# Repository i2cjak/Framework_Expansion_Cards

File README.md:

# i2cjak on X.com is THE foremost hardware engineer and poaster. he is designing one (1) new Framework Expansion Card per day until they give him a REALLY NICE laptop

# PROOF OF CHALLENGE!

## [Day 1](./Day_01_Wi-Fi-HaLow/)

Wi-Fi HaLow

## [Day 2](./Day_02_Four_Port_USB_C/)

Four Port USB-C

## [Day 3](./Day_03_ECG_SPO2/)

Electrocardiogram + SPO2

## [Day 4](./Day_04_Frameoscope/)

Frameoscope

## [Day 5](./Day_05_Power_Bus_Probe/)

USB-C I2C / Qwiic Bridge & 36V / 5A Power Telemetry Probe

## [Day 6](./Day_06_Walking_Legs/)

USB SOF-Synced 2-DOF Walking Leg Controller & Mechanical Bay Linkage (`mech/`)

## [Day 7](./Day_07_Chiptune_Synth_MIDI/)

Polyphonic FM / Chiptune 32-Bit I2S Synthesizer & Type-A MIDI Out

## [Day 8](./Day_08_CAN_Bus_Analyzer/)

1 Mbps ISO-11898 CAN 2.0B Bus Analyzer (`gs_usb` SocketCAN) & PhotoMOS 120R Termination

## [Day 9](./Day_09_Radiation_Dosimeter_RNG/)

Solid-State Dual-PIN Radiation Dosimeter, Pulse Spectrometer & Quantum Decay Hardware RNG

## [Day 10](./Day_10_SWD_Debugger_UART/)

Autoleveling 1.65V–5.5V CMSIS-DAPv2 High-Speed SWD Debugger & 6 Mbps UART Console

## [Day 11](./Day_11_ToF_Gesture_IR_Blaster/)

Dual 4m Laser Time-of-Flight Stereo Gesture Deck & Universal 940nm Phased-Arc IR Blaster

## [Day 12](./Day_12_Bench_Power_Supply/)

Programmable 1.0V–15.0V (4W) SEPIC Micro Bench Power Supply, 140µs E-Fuse & 4-Wire Kelvin Port

## [Day 13](./Day_13_LoRa_Spectrum_Sweeper/)

+22 dBm Sub-GHz LoRa Mesh Radio (`SX1262`) & 150–960 MHz ISM Spectrum Sweeper w/ Edge SMA

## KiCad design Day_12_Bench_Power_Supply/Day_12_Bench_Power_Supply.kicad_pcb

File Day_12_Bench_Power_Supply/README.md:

# Day 12 — Pocket Programmable `1.0V–15.0V` SEPIC Micro Bench Supply & Electronic Fuse

A digitally trimmed pocket DC lab rail and `140 µs` hardware electronic fuse powered from a single Framework Laptop USB-C bay (`5 V` `VBUS`), delivering a regulated **`1.00 V – 15.00 V`** (`4.0 W` continuous) output with true **`0.00 V` DC shutoff**, 4-wire Kelvin voltage sensing, `16-bit` live `V/I/P` readback, and SCPI/CLI control inside a blue ENIG `26.0 × 30.0 mm` Expansion Card.

## Hardware Architecture

1. **True-Zero-Disconnect `1.2 MHz` Dual-Inductor SEPIC Stage (`U4` `MT3608`, `L1`/`L2` `SWPA4018S100MT`, `C10`, `D3` `SS34`):**
   - Unlike a conventional boost regulator—which passes `VBUS - V_D ≈ 4.7 V` straight to the output even when disabled—the **SEPIC** topology inserts a `50 V` `2.2 µF` DC-blocking coupling capacitor (`C10`) between shielded `10 µH / 1.6 A` inductors `L1` and `L2` (`4.0 × 4.0 × 1.8 mm`), providing **galvanic DC path interruption (`0.00 V` off-state)** while stepping smoothly both **below and above `5 V` `VBUS`** (`1.00 V` to `15.00 V`) into a `4× 2.2 µF / 50 V` low-ESR ceramic bank (`C11`–`C13`, `C15`) with an `18 V` `BZT52C18` overvoltage Zener clamp (`D6`).

2. **`12-Bit` DAC Feedback Injection & Closed-Loop Millivolt Trim (`U5` `MCP4725A0T-E/CH`):**
   - Injects a rail-to-rail `0–3.30 V` 12-bit DAC output (`0x60`) through `R18` (`22 kΩ 1%`) into the `MT3608` `0.600 V` feedback summing node alongside `R16` (`100 kΩ 1%` to `VOUT_SENSE`) and `R17` (`5.1 kΩ 1%` to `GND`), yielding **`3.66 mV / LSB`** native resolution across `1.00 V – 15.00 V`, continuously trimmed against `INA226` `1.25 mV` bus readback.

3. **Pulsed `25 kHz` PWM Input Soft-Start & `140 µs` Hardware Electronic Fuse (`Q1` `AO3401A`, `Q2` `AO3400A`, `U6` `INA226AIDGSR`, `R19` `50 mΩ`):**
   - Always-on `3.3 V` control power (`U2` `XC6206P332MR-G`) keeps the MCU, DAC, and telemetry alive while `Q1` (`AO3401A` high-side P-FET driven via `Q2` `AO3400A` on `PB0` / `TIM3_CH3`) precharges `C7` (`10 µF`) over `12 ms` (`< 0.15 A` peak inrush, verified via `PA1` `ADC_IN1` host `VBUS` droop sensing) and clamps continuous input draw below `0.95 A` (`4.0 W` output budget, safe on both `1.5 A` and `3.0 A` Framework USB-C ports).
   - High-side `INA226AIDGSR` (`0x40`) across `R19` (`50 mΩ 1%`, `50 µA / LSB`) fires its hardware Shunt-Over-Voltage (`SOL`) `~Alert` into `PA0` (`EXTI0`) in **`140 µs`**, killing `SEPIC_EN` (`PB1`) and opening `Q1` in `< 2 µs` ISR latency while latching the bezel `FLT` LED (`D5`).

4. **4-Wire Kelvin Bezel Output Port & Crystal-Less USB SCPI Controller (`J3` `SM04B-SRSS-TB`, `U3` `STM32F072CBT6`):**
   - Outward 4-pin `1.0 mm` right-angle header (`J3`: `VOUT`, `VOUT_SENSE` with `100 Ω` local Kelvin bridge `R21`, `GND`, `GND`) compensates lead drop right at the load, controlled over crystal-less USB 2.0 FS `CDC-ACM` (`U1` `D3V3XA4B10LP-7` + `D1` `H5VL10B`).

## Fabrication & Firmware Build

All `44` SMT components are sourced from the fab's stock on a `0.8 mm` 4-layer Blue ENIG stackup (`Day_12_Bench_Power_Supply.fab.json`).

```bash
# Regenerate ERC/DRC reports, Gerbers, BOM/CPL, STEP model, and 3D renders
python3 build.py

# Compile bare-metal STM32F072CBT6 SEPIC DAC Trim + 140us E-Fuse firmware
make -C firmware
```

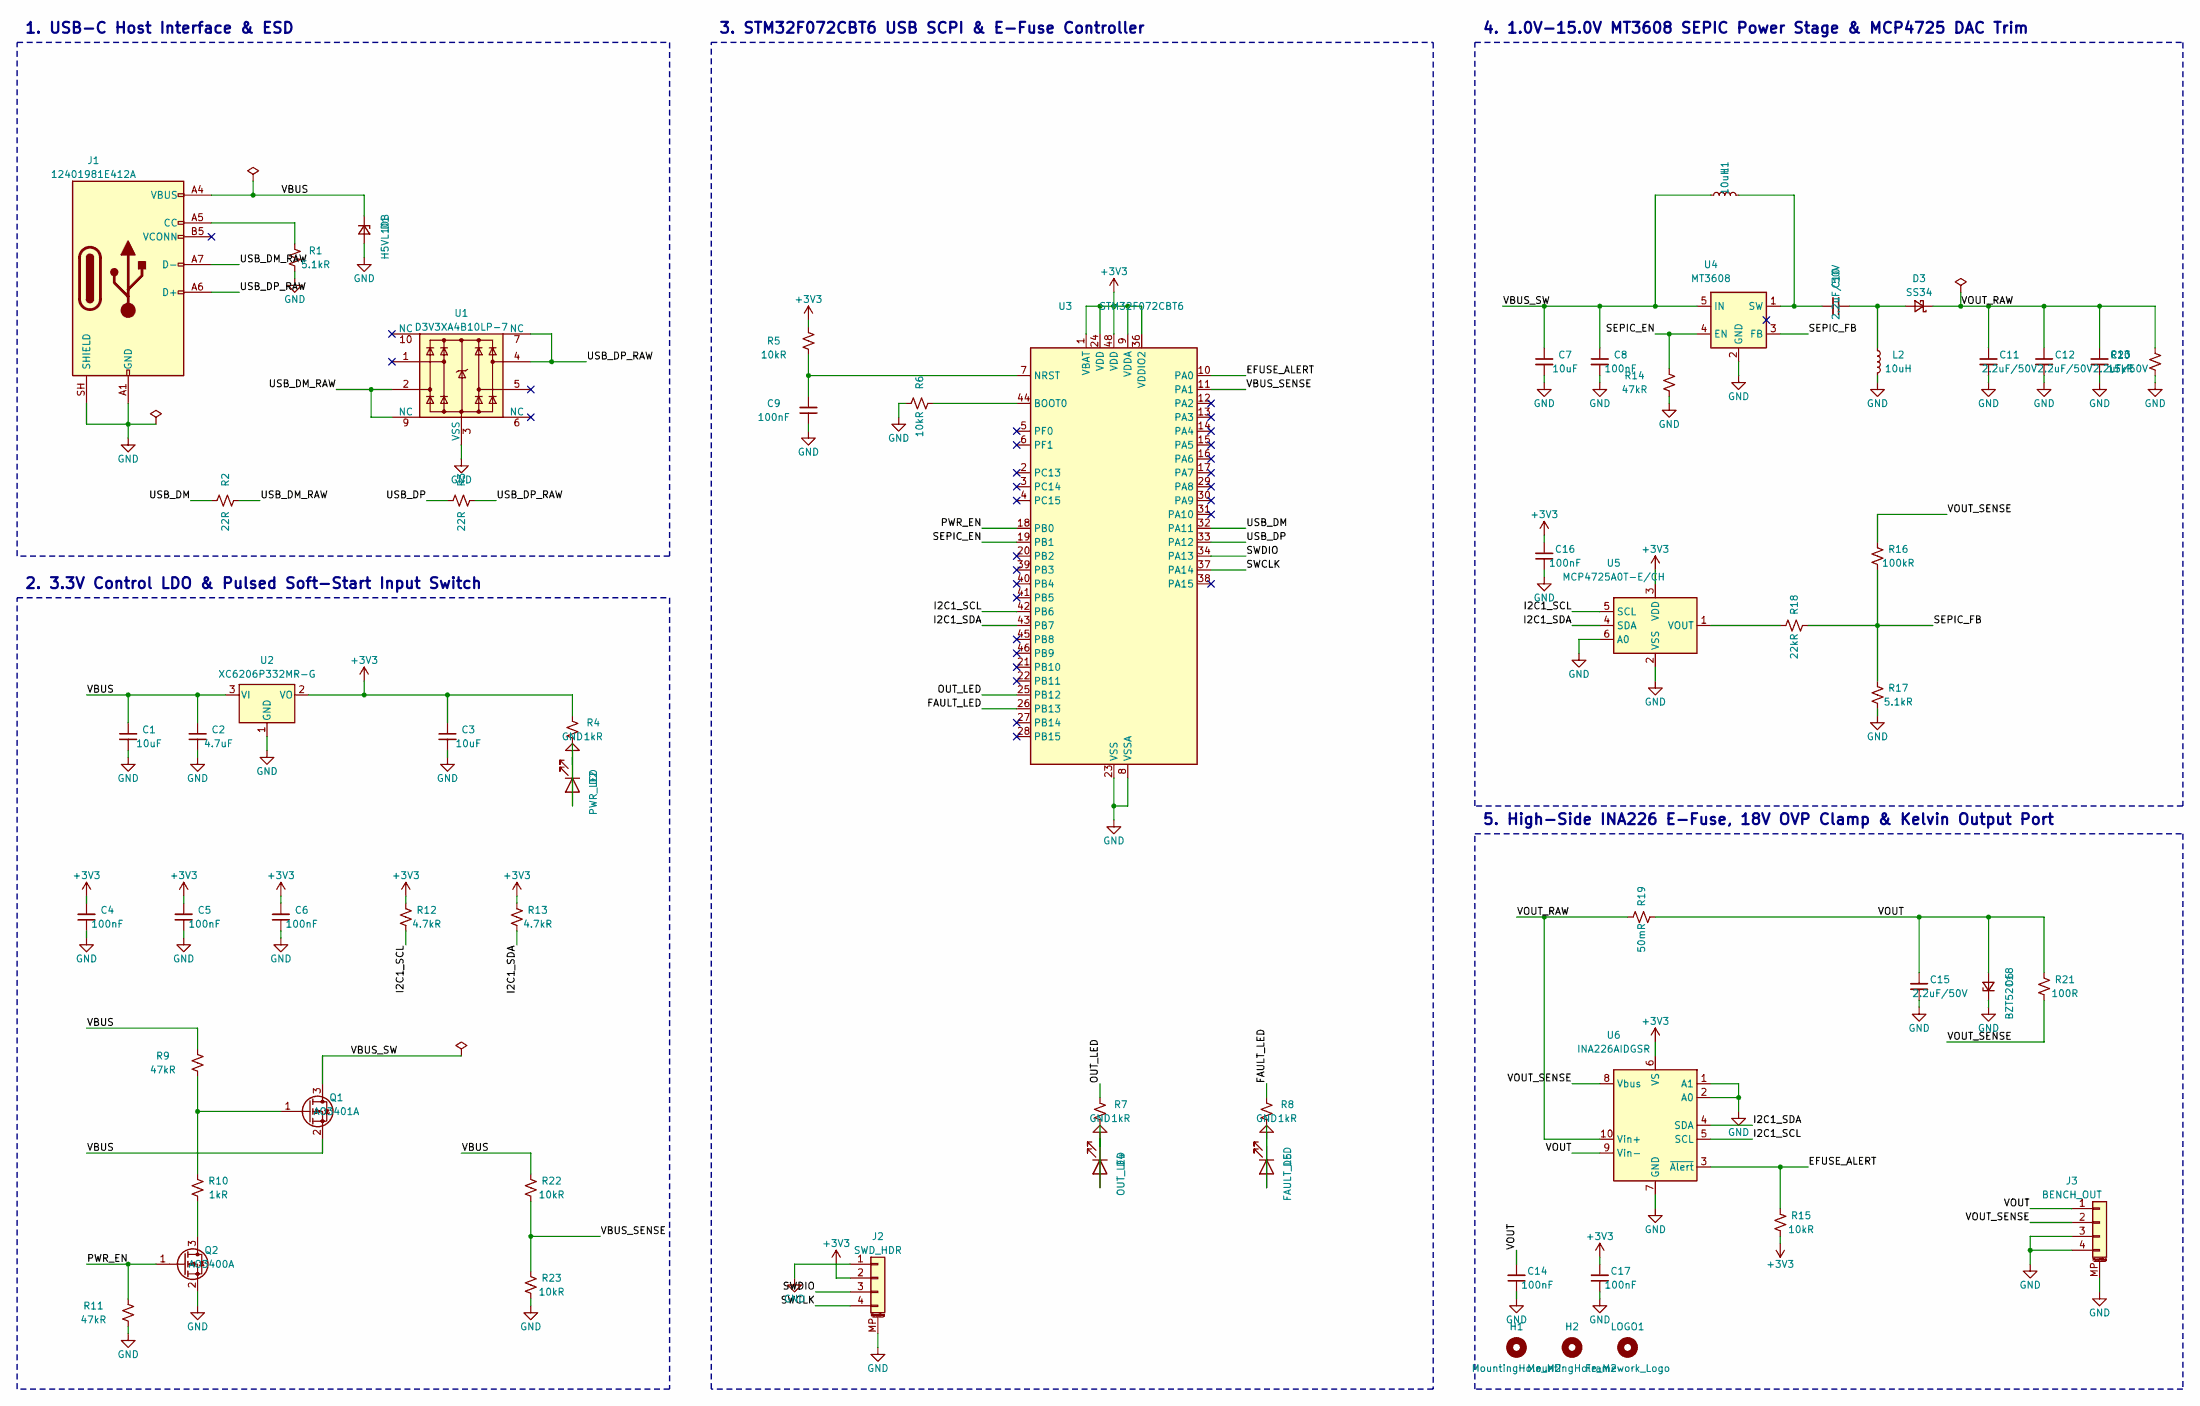
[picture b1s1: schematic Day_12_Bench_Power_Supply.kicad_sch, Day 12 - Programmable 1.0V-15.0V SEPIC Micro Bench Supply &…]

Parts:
C1, C3, C7: 10uF; C_0805_2012Metric; MPN CL21A106KAYNNNE; LCSC C15850
C2: 4.7uF; C_0603_1608Metric; MPN CL10A475KO8NNNC; LCSC C19666
C4, C5, C6, C8, C9, C14, C16, C17: 100nF; C_0402_1005Metric; MPN CL05B104KB54PNC; LCSC C307331
C10, C11, C12, C13, C15: 2.2uF/50V; C_0805_2012Metric; MPN CL21A225KBQNNNE; LCSC C377773
D1: H5VL10B; D_SOD-882; MPN H5VL10B; LCSC C7420372
D2: PWR_LED; LED_0603_1608Metric; MPN KT-0603G; LCSC C2297
D3: SS34; D_SMA; MPN SS34; LCSC C8678
D4: OUT_LED; LED_0603_1608Metric; MPN KT-0603G; LCSC C2297
D5: FAULT_LED; LED_0603_1608Metric; MPN KT-0603R; LCSC C2286
D6: BZT52C18; D_SOD-123; MPN BZT52C18; LCSC C19077414
H1, H2: MountingHole_M2; MountingHole_2.2mm_M2
J1: 12401981E412A; USB_C_Plug_Amphenol_12401981E412A; MPN 12401981E412A; LCSC C5428559
J2: SWD_HDR; JST_SH_SM04B-SRSS-TB_1x04-1MP_P1.00mm_Horizontal; MPN SM04B-SRSS-TB(LF)(SN); LCSC C160404
J3: BENCH_OUT; JST_SH_SM04B-SRSS-TB_1x04-1MP_P1.00mm_Horizontal; MPN SM04B-SRSS-TB(LF)(SN); LCSC C160404
L1, L2: 10uH; L_Sunlord_SWPA4018S; MPN SWPA4018S100MT; LCSC C83442
LOGO1: Framework_Logo; Framework-Logo_1.5mm_SilkScreen
Q1: AO3401A; SOT-23; MPN AO3401A; LCSC C15127
Q2: AO3400A; SOT-23; MPN AO3400A; LCSC C20917
R1, R17: 5.1kR; R_0402_1005Metric; MPN 0402WGF5101TCE; LCSC C25905
R2, R3: 22R; R_0402_1005Metric; MPN 0402WGF220JTCE; LCSC C25092
R4, R7, R8, R10: 1kR; R_0402_1005Metric; MPN 0402WGF1001TCE; LCSC C11702
R5, R6, R15, R22, R23: 10kR; R_0402_1005Metric; MPN 0402WGF1002TCE; LCSC C25744
R9, R11, R14: 47kR; R_0402_1005Metric; MPN 0402WGF4702TCE; LCSC C25792
R12, R13: 4.7kR; R_0402_1005Metric; MPN 0402WGF4701TCE; LCSC C25900
R16: 100kR; R_0402_1005Metric; MPN 0402WGF1003TCE; LCSC C25741
R18: 22kR; R_0402_1005Metric; MPN 0402WGF2202TCE; LCSC C25768
R19: 50mR; R_0805_2012Metric; MPN 0805W4F500MT5E; LCSC C247602
R20: 15kR; R_0402_1005Metric; MPN 0402WGF1502TCE; LCSC C25756
R21: 100R; R_0402_1005Metric; MPN 0402WGF1000TCE; LCSC C25076
U1: D3V3XA4B10LP-7; Diodes_UDFN-10_1x2.5mm_P0.5mm; MPN D3V3XA4B10LP-7; LCSC C1980462
U2: XC6206P332MR-G; SOT-23; MPN XC6206P332MR-G; LCSC C5446
U3: STM32F072CBT6; LQFP-48_7x7mm_P0.5mm; MPN STM32F072CBT6; LCSC C81720
U4: MT3608; SOT-23-6; MPN MT3608; LCSC C84817
U5: MCP4725A0T-E/CH; SOT-23-6; MPN MCP4725A0T-E/CH; LCSC C144198
U6: INA226AIDGSR; MSOP-10_3x3mm_P0.5mm; MPN INA226AIDGSR; LCSC C64893

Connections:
/EFUSE_ALERT: R15.1, U3.10 (PA0), U6.3 (~Alert)
/FAULT_LED: R8.1, U3.26 (PB13)
/I2C1_SCL: R12.2, U3.42 (PB6), U5.5 (SCL), U6.5 (SCL)
/I2C1_SDA: R13.2, U3.43 (PB7), U5.4 (SDA), U6.4 (SDA)
/OUT_LED: R7.1, U3.25 (PB12)
/PWR_EN: Q2.1 (G), R11.1, U3.18 (PB0)
/SEPIC_EN: R14.1, U3.19 (PB1), U4.4 (EN)
/SEPIC_FB: R16.2, R17.1, R18.2, U4.3 (FB)
/SWCLK: J2.4, U3.37 (PA14)
/SWDIO: J2.3, U3.34 (PA13)
/USB_DM: R2.1, U3.32 (PA11)
/USB_DM_RAW: J1.A7 (D-), R2.2, U1.2, U1.9 (NC)
/USB_DP: R3.1, U3.33 (PA12)
/USB_DP_RAW: J1.A6 (D+), R3.2, U1.4, U1.7 (NC)
/VBUS: C1.1, C2.1, D1.1 (K), J1.A4 (VBUS), J1.A9 (VBUS), J1.B4 (VBUS), J1.B9 (VBUS), Q1.2 (S), R9.1, R22.1, U2.3 (VI)
/VBUS_SENSE: R22.2, R23.1, U3.11 (PA1)
/VBUS_SW: C7.1, C8.1, L1.1, Q1.3 (D), U4.5 (IN)
/VOUT: C14.1, C15.1, D6.2 (A), J3.1, R19.2, R21.1, U6.9 (Vin-)
/VOUT_RAW: C11.1, C12.1, C13.1, D3.1 (K), R19.1, R20.1, U6.10 (Vin+)
/VOUT_SENSE: J3.2, R16.1, R21.2, U6.8 (Vbus)
unnamed: C10.2, D3.2 (A), L2.1
unnamed: J1.A5 (CC), R1.1
unnamed: Q1.1 (G), R9.2, R10.1
unnamed: Q2.3 (D), R10.2
unnamed: R6.2, U3.44 (BOOT0)
unnamed: C9.1, R5.2, U3.7 (NRST)
unnamed: C10.1, L1.2, U4.1 (SW)
unnamed: R18.1, U5.1 (VOUT)

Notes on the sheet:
1. USB-C Host Interface & ESD
2. 3.3V Control LDO & Pulsed Soft-Start Input Switch
3. STM32F072CBT6 USB SCPI & E-Fuse Controller
4. 1.0V-15.0V MT3608 SEPIC Power Stage & MCP4725 DAC Trim
5. High-Side INA226 E-Fuse, 18V OVP Clamp & Kelvin Output Port

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
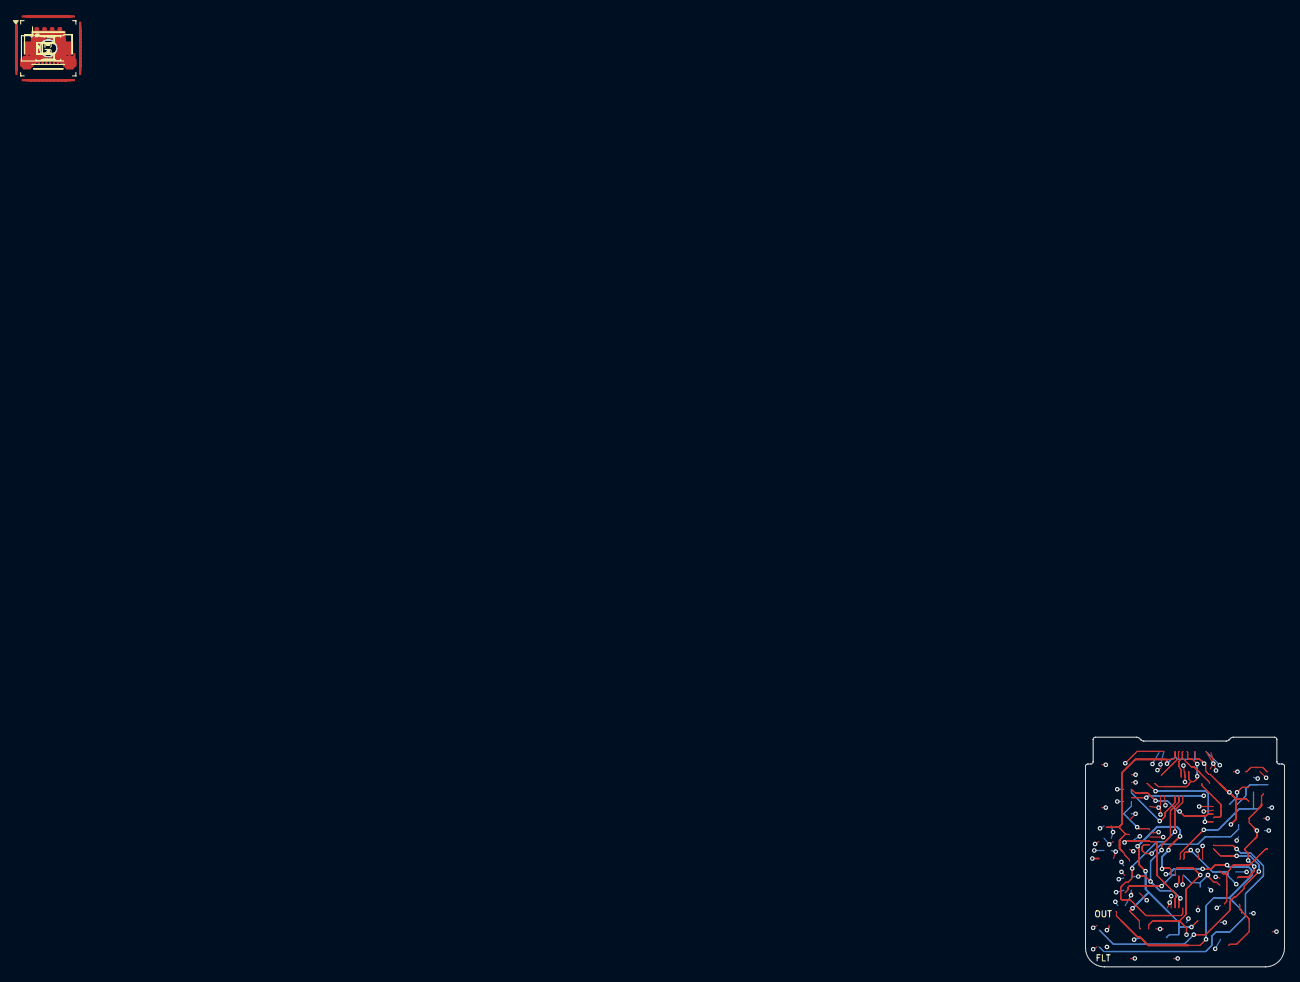
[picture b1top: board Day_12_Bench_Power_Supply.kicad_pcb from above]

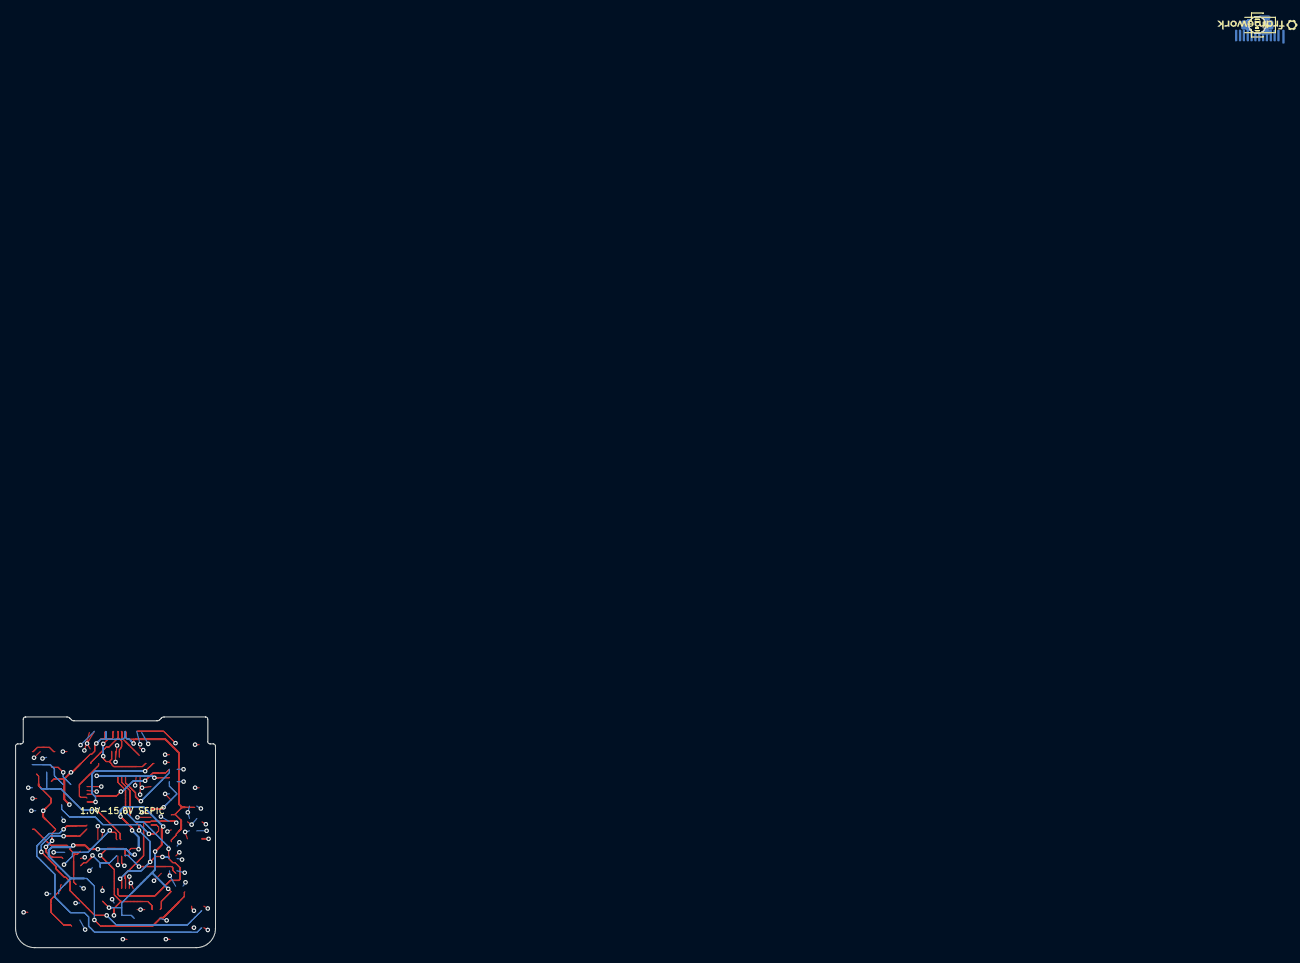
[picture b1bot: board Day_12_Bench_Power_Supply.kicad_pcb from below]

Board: 4 copper layers, 26.0 x 30.0 mm, 62 parts (32 on the bottom side), 33 nets.

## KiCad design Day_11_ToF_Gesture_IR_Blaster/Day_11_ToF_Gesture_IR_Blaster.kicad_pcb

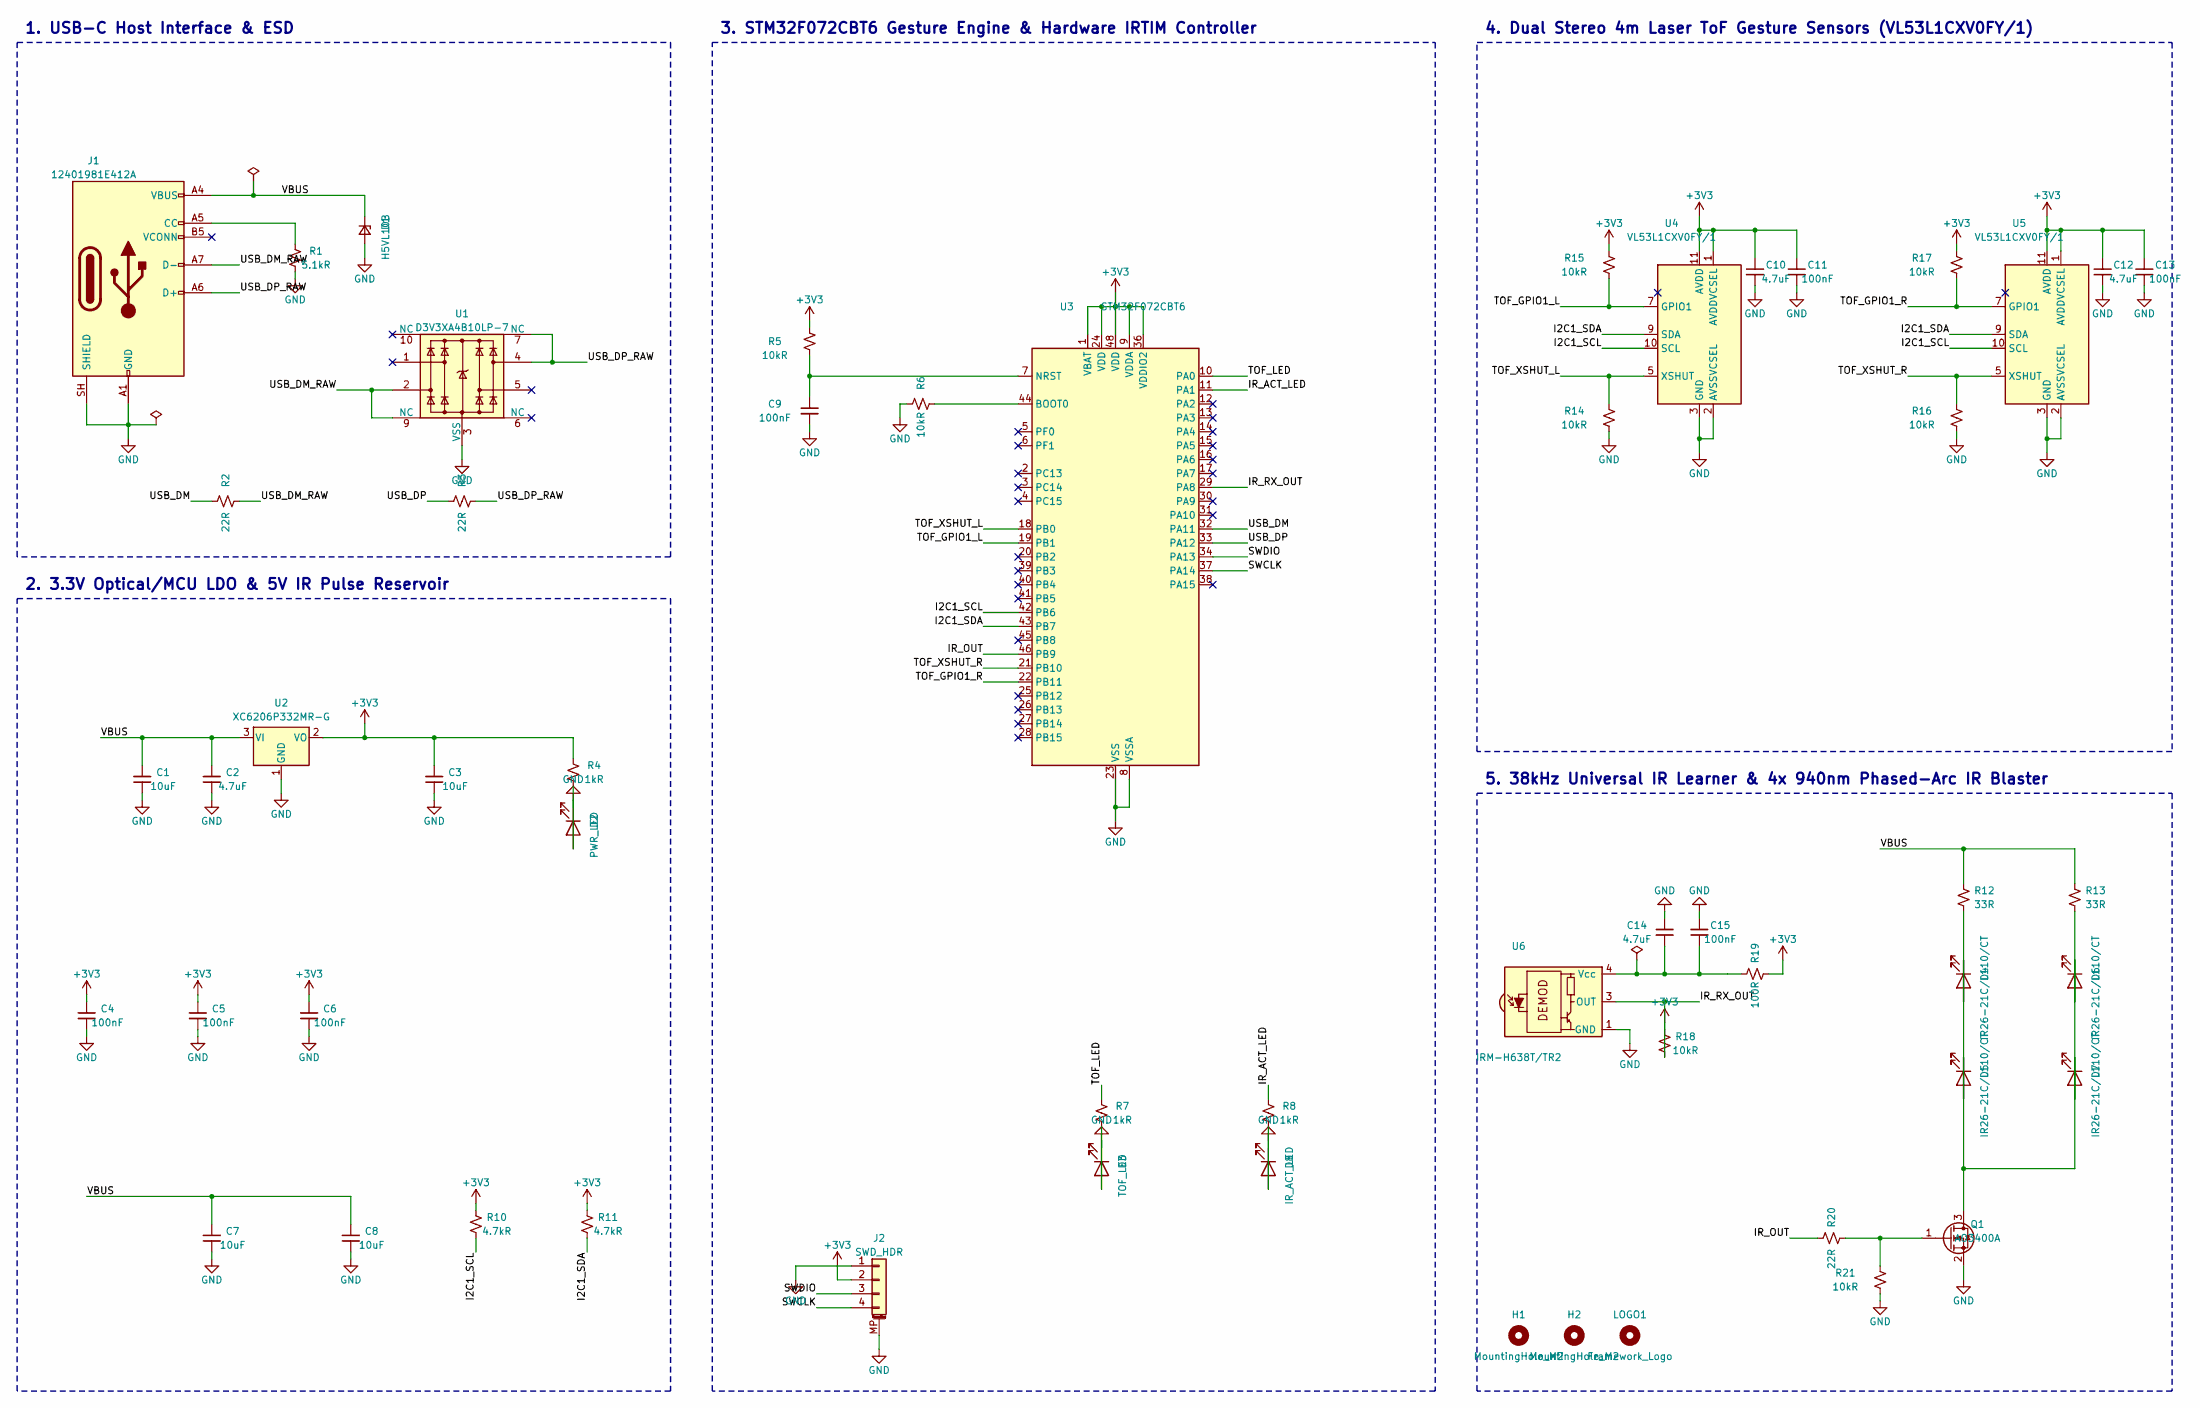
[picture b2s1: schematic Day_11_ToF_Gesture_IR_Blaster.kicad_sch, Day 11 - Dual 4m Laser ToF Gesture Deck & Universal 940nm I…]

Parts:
C1, C3, C7, C8: 10uF; C_0805_2012Metric; MPN CL21A106KAYNNNE; LCSC C15850
C2, C10, C12, C14: 4.7uF; C_0603_1608Metric; MPN CL10A475KO8NNNC; LCSC C19666
C4, C5, C6, C9, C11, C13, C15: 100nF; C_0402_1005Metric; MPN CL05B104KB54PNC; LCSC C307331
D1: H5VL10B; D_SOD-882; MPN H5VL10B; LCSC C7420372
D2: PWR_LED; LED_0603_1608Metric; MPN KT-0603G; LCSC C2297
D3: TOF_LED; LED_0603_1608Metric; MPN KT-0603W; LCSC C2290
D4, D5, D6, D7: IR26-21C/L110/CT; LED_1206_3216Metric; MPN IR26-21C/L110/CT; LCSC C131280
D8: IR_ACT_LED; LED_0603_1608Metric; MPN KT-0603R; LCSC C2286
H1, H2: MountingHole_M2; MountingHole_2.2mm_M2
J1: 12401981E412A; USB_C_Plug_Amphenol_12401981E412A; MPN 12401981E412A; LCSC C5428559
J2: SWD_HDR; JST_SH_SM04B-SRSS-TB_1x04-1MP_P1.00mm_Horizontal; MPN SM04B-SRSS-TB(LF)(SN); LCSC C160404
LOGO1: Framework_Logo; Framework-Logo_1.5mm_SilkScreen
Q1: AO3400A; SOT-23; MPN AO3400A; LCSC C20917
R1: 5.1kR; R_0402_1005Metric; MPN 0402WGF5101TCE; LCSC C25905
R2, R3, R20: 22R; R_0402_1005Metric; MPN 0402WGF220JTCE; LCSC C25092
R4, R7, R8: 1kR; R_0402_1005Metric; MPN 0402WGF1001TCE; LCSC C11702
R5, R6, R14, R15, R16, R17, R18, R21: 10kR; R_0402_1005Metric; MPN 0402WGF1002TCE; LCSC C25744
R10, R11: 4.7kR; R_0402_1005Metric; MPN 0402WGF4701TCE; LCSC C25900
R12, R13: 33R; R_0603_1608Metric; MPN 0603WAF330JT5E; LCSC C23140
R19: 100R; R_0402_1005Metric; MPN 0402WGF1000TCE; LCSC C25076
U1: D3V3XA4B10LP-7; Diodes_UDFN-10_1x2.5mm_P0.5mm; MPN D3V3XA4B10LP-7; LCSC C1980462
U2: XC6206P332MR-G; SOT-23; MPN XC6206P332MR-G; LCSC C5446
U3: STM32F072CBT6; LQFP-48_7x7mm_P0.5mm; MPN STM32F072CBT6; LCSC C81720
U4, U5: VL53L1CXV0FY/1; ST_VL53L1x; MPN VL53L1CXV0FY/1; LCSC C190004
U6: IRM-H638T/TR2; Everlight_IRM-H6xxT; MPN IRM-H638T/TR2; LCSC C91447

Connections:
/I2C1_SCL: R10.2, U3.42 (PB6), U4.10 (SCL), U5.10 (SCL)
/I2C1_SDA: R11.2, U3.43 (PB7), U4.9 (SDA), U5.9 (SDA)
/IR_ACT_LED: R8.1, U3.11 (PA1)
/IR_OUT: R20.1, U3.46 (PB9)
/SWCLK: J2.4, U3.37 (PA14)
/SWDIO: J2.3, U3.34 (PA13)
/TOF_GPIO1_L: R15.2, U3.19 (PB1), U4.7 (GPIO1)
/TOF_GPIO1_R: R17.2, U3.22 (PB11), U5.7 (GPIO1)
/TOF_LED: R7.1, U3.10 (PA0)
/TOF_XSHUT_L: R14.1, U3.18 (PB0), U4.5 (XSHUT)
/TOF_XSHUT_R: R16.1, U3.21 (PB10), U5.5 (XSHUT)
/USB_DM: R2.1, U3.32 (PA11)
/USB_DM_RAW: J1.A7 (D-), R2.2, U1.2, U1.9 (NC)
/USB_DP: R3.1, U3.33 (PA12)
/USB_DP_RAW: J1.A6 (D+), R3.2, U1.4, U1.7 (NC)
/VBUS: C1.1, C2.1, C7.1, C8.1, D1.1 (K), J1.A4 (VBUS), J1.A9 (VBUS), J1.B4 (VBUS), J1.B9 (VBUS), R12.1, R13.1, U2.3 (VI)
unnamed: D4.2 (A), R12.2
unnamed: D4.1 (K), D5.2 (A)
unnamed: D5.1 (K), D7.1 (K), Q1.3 (D)
unnamed: D6.2 (A), R13.2
unnamed: D6.1 (K), D7.2 (A)
unnamed: J1.A5 (CC), R1.1
unnamed: Q1.1 (G), R20.2, R21.1
unnamed: R6.2, U3.44 (BOOT0)
unnamed: C9.1, R5.2, U3.7 (NRST)
unnamed: C14.1, C15.1, R19.1, U6.4 (Vcc)

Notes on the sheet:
1. USB-C Host Interface & ESD
2. 3.3V Optical/MCU LDO & 5V IR Pulse Reservoir
3. STM32F072CBT6 Gesture Engine & Hardware IRTIM Controller
4. Dual Stereo 4m Laser ToF Gesture Sensors (VL53L1CXV0FY/1)
5. 38kHz Universal IR Learner & 4x 940nm Phased-Arc IR Blaster

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
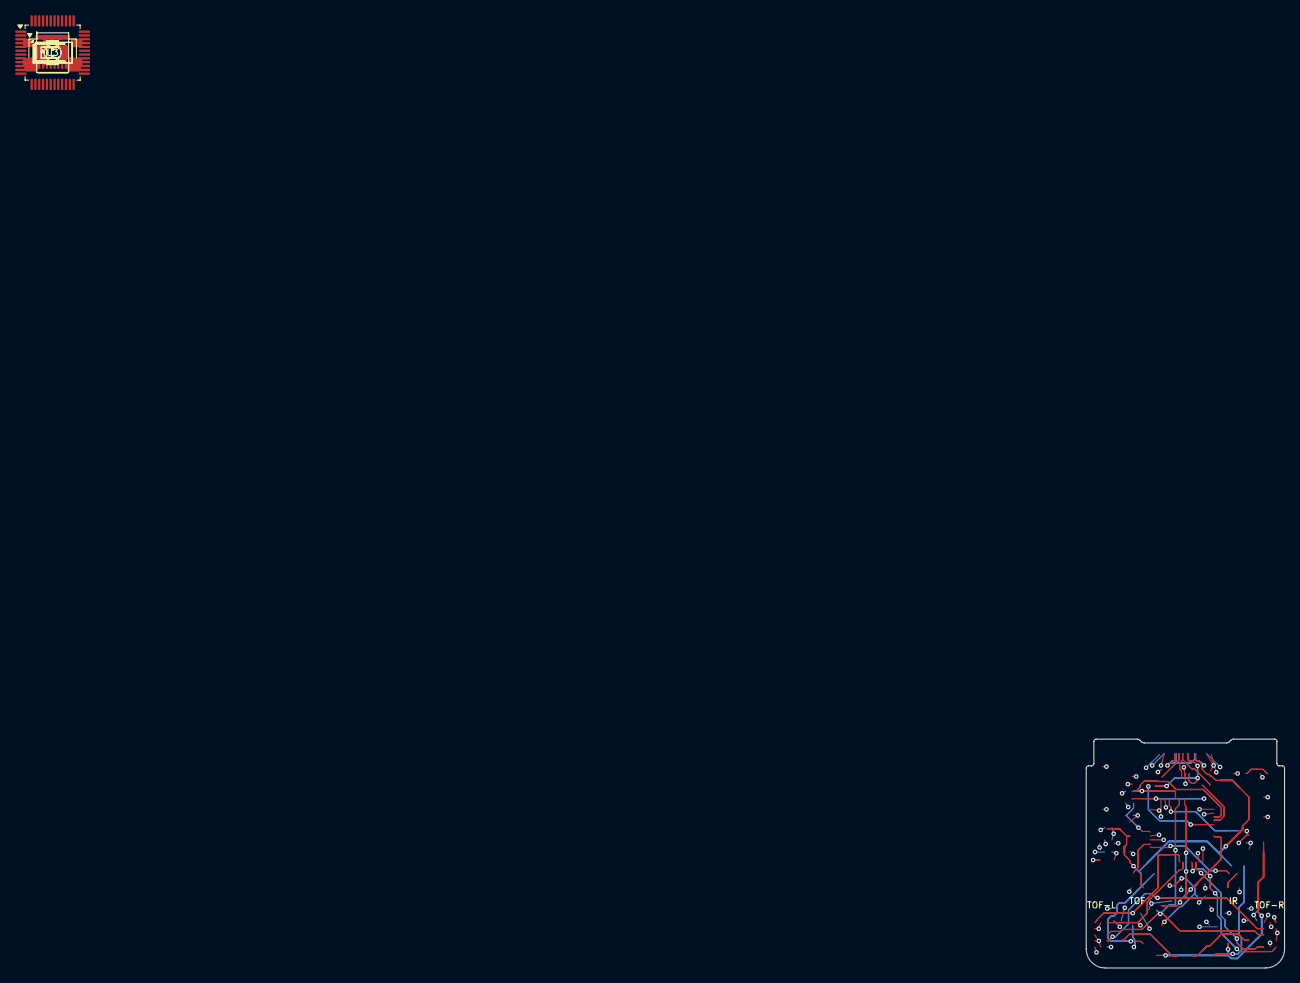
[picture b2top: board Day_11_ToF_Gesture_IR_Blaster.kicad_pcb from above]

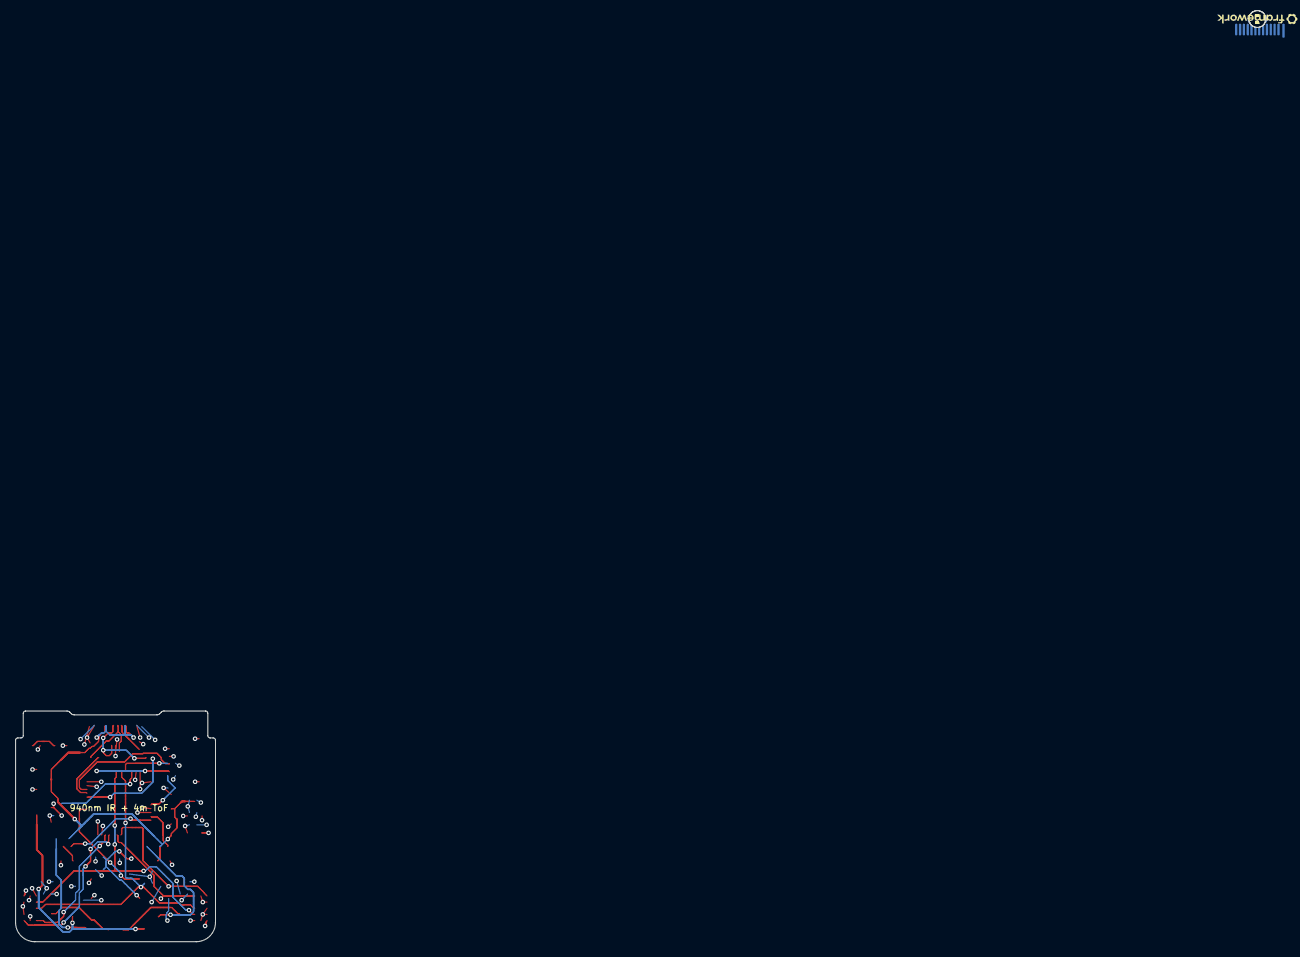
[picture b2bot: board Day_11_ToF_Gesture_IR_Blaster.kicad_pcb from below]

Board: 4 copper layers, 26.0 x 30.0 mm, 55 parts (25 on the bottom side), 32 nets.
